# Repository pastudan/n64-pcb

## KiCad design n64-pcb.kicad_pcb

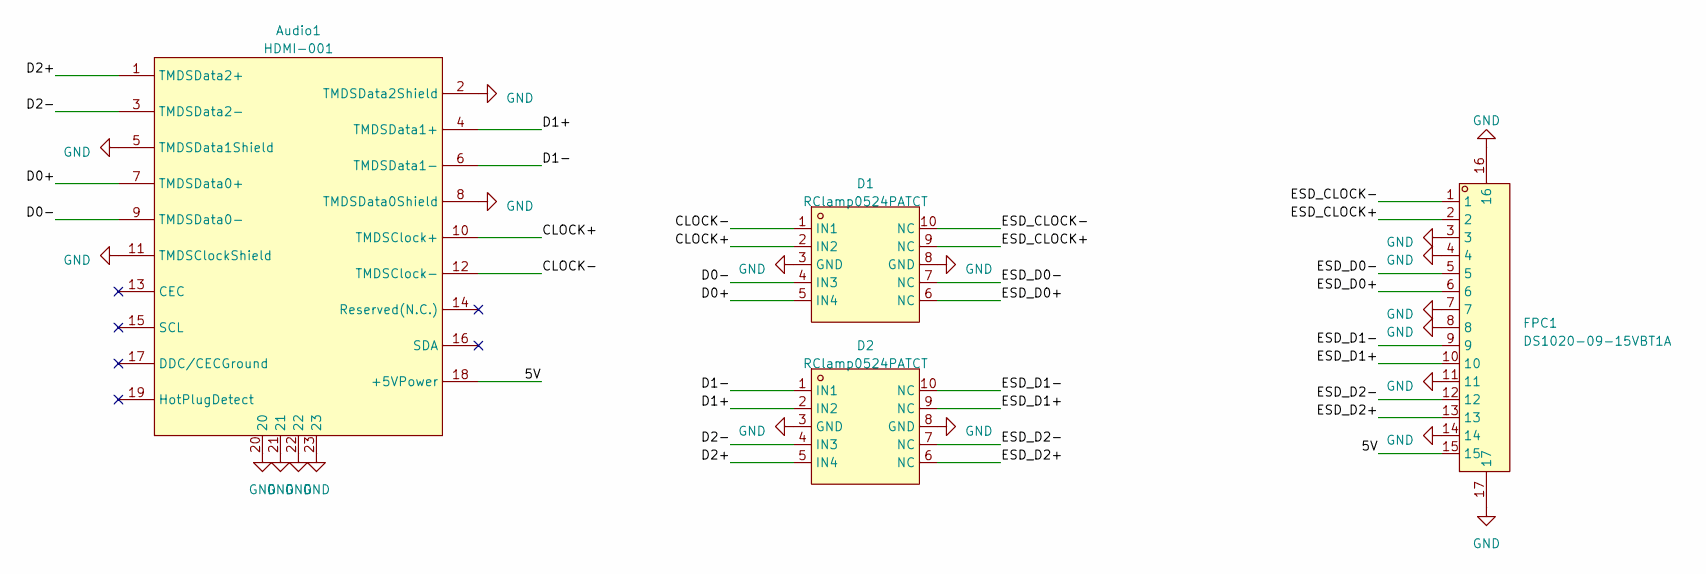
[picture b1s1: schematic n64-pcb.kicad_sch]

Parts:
Audio1: HDMI-001; HDMI-SMD_19P-P0.50-H-F; LCSC Part C138388
D1, D2: RClamp0524PATCT; SLP2510P8_L2.5-W1.0-P0.50-BL; LCSC Part C40960
FPC1: DS1020-09-15VBT1A; FPC-SMD_P0.50-15P_LSXJ-H2.0-15P; LCSC Part C94918

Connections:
/5V: Audio1.18 (+5VPower), FPC1.15
/CLOCK+: Audio1.10 (TMDSClock+), D1.2 (IN2)
/CLOCK-: Audio1.12 (TMDSClock-), D1.1 (IN1)
/D0+: Audio1.7 (TMDSData0+), D1.5 (IN4)
/D0-: Audio1.9 (TMDSData0-), D1.4 (IN3)
/D1+: Audio1.4 (TMDSData1+), D2.2 (IN2)
/D1-: Audio1.6 (TMDSData1-), D2.1 (IN1)
/D2+: Audio1.1 (TMDSData2+), D2.5 (IN4)
/D2-: Audio1.3 (TMDSData2-), D2.4 (IN3)
/ESD_CLOCK+: D1.9 (NC), FPC1.2
/ESD_CLOCK-: D1.10 (NC), FPC1.1
/ESD_D0+: D1.6 (NC), FPC1.6
/ESD_D0-: D1.7 (NC), FPC1.5
/ESD_D1+: D2.9 (NC), FPC1.10
/ESD_D1-: D2.10 (NC), FPC1.9
/ESD_D2+: D2.6 (NC), FPC1.13
/ESD_D2-: D2.7 (NC), FPC1.12
GND: Audio1.2 (TMDSData2Shield), Audio1.5 (TMDSData1Shield), Audio1.8 (TMDSData0Shield), Audio1.11 (TMDSClockShield), Audio1.20, Audio1.21, Audio1.22, Audio1.23, D1.3 (GND), D1.8 (GND), D2.3 (GND), D2.8 (GND), FPC1.3, FPC1.4, FPC1.7, FPC1.8, FPC1.11, FPC1.14, FPC1.16, FPC1.17

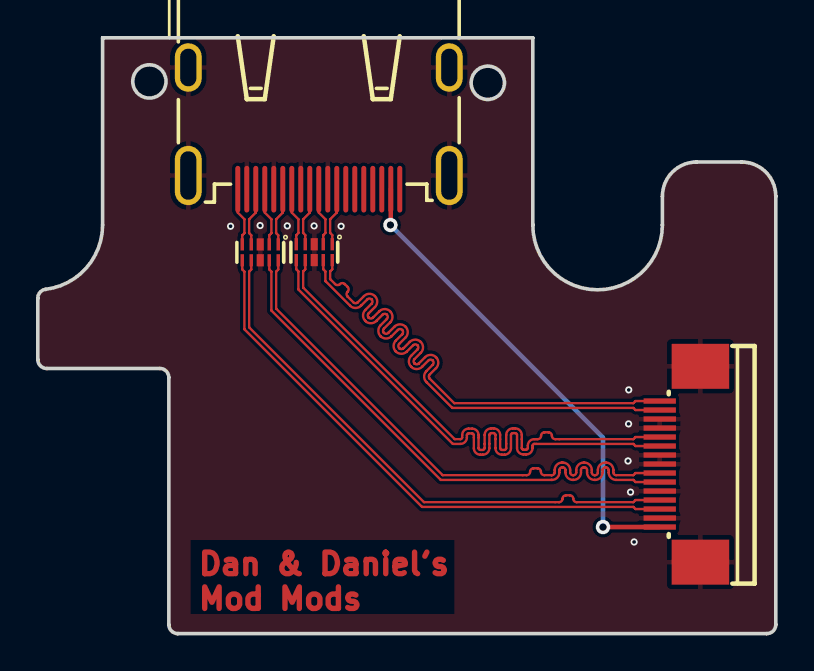
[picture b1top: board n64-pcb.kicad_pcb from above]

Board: 4 copper layers, 41.0 x 33.1 mm, 4 parts (0 on the bottom side), 18 nets.

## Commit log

2023-05-15 update gitignore
2023-05-15 diff pair length matching
